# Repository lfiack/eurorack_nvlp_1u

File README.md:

# Eurorack NVLP 1U
Single Attack/Release envelope generator based on an STM32

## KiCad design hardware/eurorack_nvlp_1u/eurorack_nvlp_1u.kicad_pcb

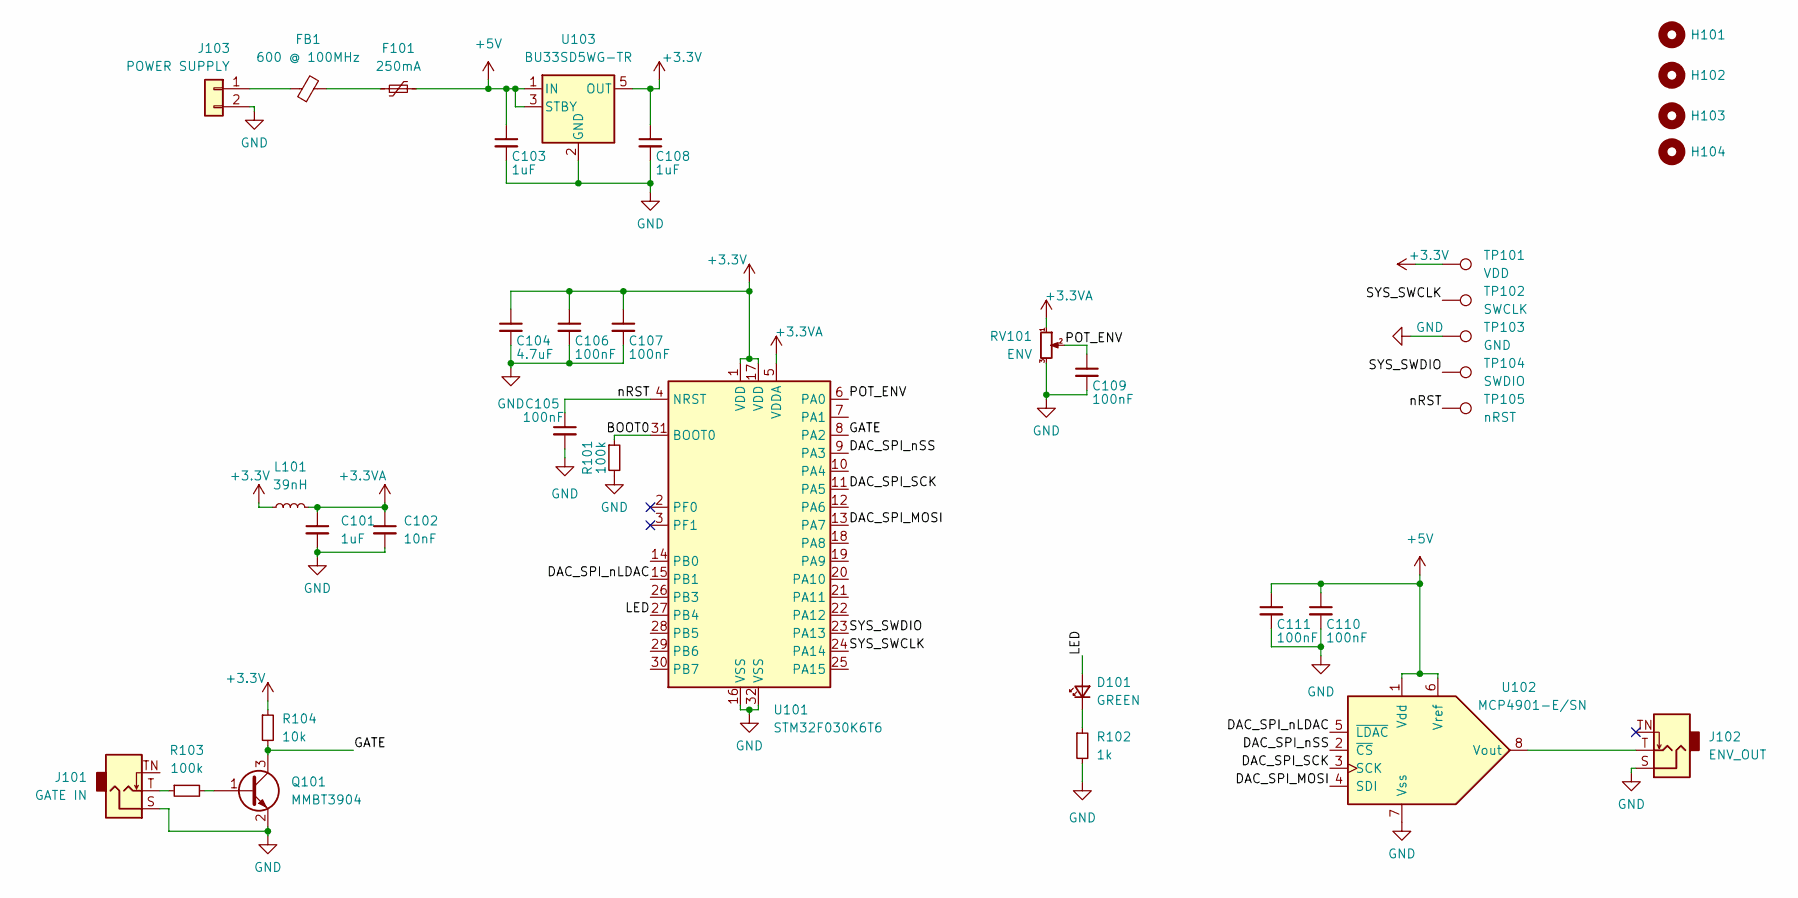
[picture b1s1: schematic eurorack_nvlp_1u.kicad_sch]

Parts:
C101, C103, C108: 1uF; C_0603_1608Metric
C102: 10nF; C_0603_1608Metric
C104: 4.7uF; C_0603_1608Metric
C105, C106, C107, C109, C110, C111: 100nF; C_0603_1608Metric
D101: GREEN; LED_0603_1608Metric
F101: 250mA; Fuse_1206_3216Metric; Farnell 2834880
FB1: 600 @ 100MHz; L_0805_2012Metric_Pad1.15x1.40mm_HandSolder; Farnell 2292460
H101, H102, H103, H104: MountingHole; MountingHole_3.2mm_M3
J101: GATE IN; Jack_3.5mm_QingPu_WQP-PJ398SM_Vertical_CircularHoles
J102: ENV_OUT; Jack_3.5mm_QingPu_WQP-PJ398SM_Vertical_CircularHoles
J103: POWER SUPPLY; JST_XH_B2B-XH-A_1x02_P2.50mm_Vertical
L101: 39nH; L_0603_1608Metric
Q101: MMBT3904; SOT-23
R101, R103: 100k; R_0603_1608Metric
R102: 1k; R_0603_1608Metric
R104: 10k; R_0603_1608Metric
RV101: ENV; Potentiometer_Alpha_RD901F-40-00D_Single_Vertical
TP101: VDD; TestPoint_Pad_D1.5mm
TP102: SWCLK; TestPoint_Pad_D1.5mm
TP103: GND; TestPoint_Pad_D1.5mm
TP104: SWDIO; TestPoint_Pad_D1.5mm
TP105: nRST; TestPoint_Pad_D1.5mm
U101: STM32F030K6T6; LQFP-32_7x7mm_P0.8mm
U102: MCP4901-E/SN; SOIC-8_3.9x4.9mm_P1.27mm
U103: BU33SD5WG-TR; SOT-23-5

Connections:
+3.3V: C104.1, C106.1, C107.1, C108.1, L101.1, R104.1, TP101.1, U101.1 (VDD), U101.17 (VDD), U103.5 (OUT)
+3.3VA: C101.1, C102.1, L101.2, RV101.1, U101.5 (VDDA)
+5V: C103.1, C110.1, C111.1, F101.2, U102.1 (Vdd), U102.6 (Vref), U103.1 (IN), U103.3 (STBY)
/BOOT0: R101.1, U101.31 (BOOT0)
/DAC_SPI_MOSI: U101.13 (PA7), U102.4 (SDI)
/DAC_SPI_SCK: U101.11 (PA5), U102.3 (SCK)
/DAC_SPI_nLDAC: U101.15 (PB1), U102.5 (~LDAC)
/DAC_SPI_nSS: U101.9 (PA3), U102.2 (~CS)
/GATE: Q101.3 (C), R104.2, U101.8 (PA2)
/LED: D101.2 (A), U101.27 (PB4)
/POT_ENV: C109.1, RV101.2, U101.6 (PA0)
/SYS_SWCLK: TP102.1, U101.24 (PA14)
/SYS_SWDIO: TP104.1, U101.23 (PA13)
/nRST: C105.1, TP105.1, U101.4 (NRST)
GND: C101.2, C102.2, C103.2, C104.2, C105.2, C106.2, C107.2, C108.2, C109.2, C110.2, C111.2, J101.S, J102.S, J103.2, Q101.2 (E), R101.2, R102.2, RV101.3, TP103.1, U101.16 (VSS), U101.32 (VSS), U102.7 (Vss), U103.2 (GND)
unnamed: D101.1 (K), R102.1
unnamed: F101.1, FB1.2
unnamed: J101.T, R103.1
unnamed: J102.T, U102.8 (Vout)
unnamed: FB1.1, J103.1
unnamed: Q101.1 (B), R103.2

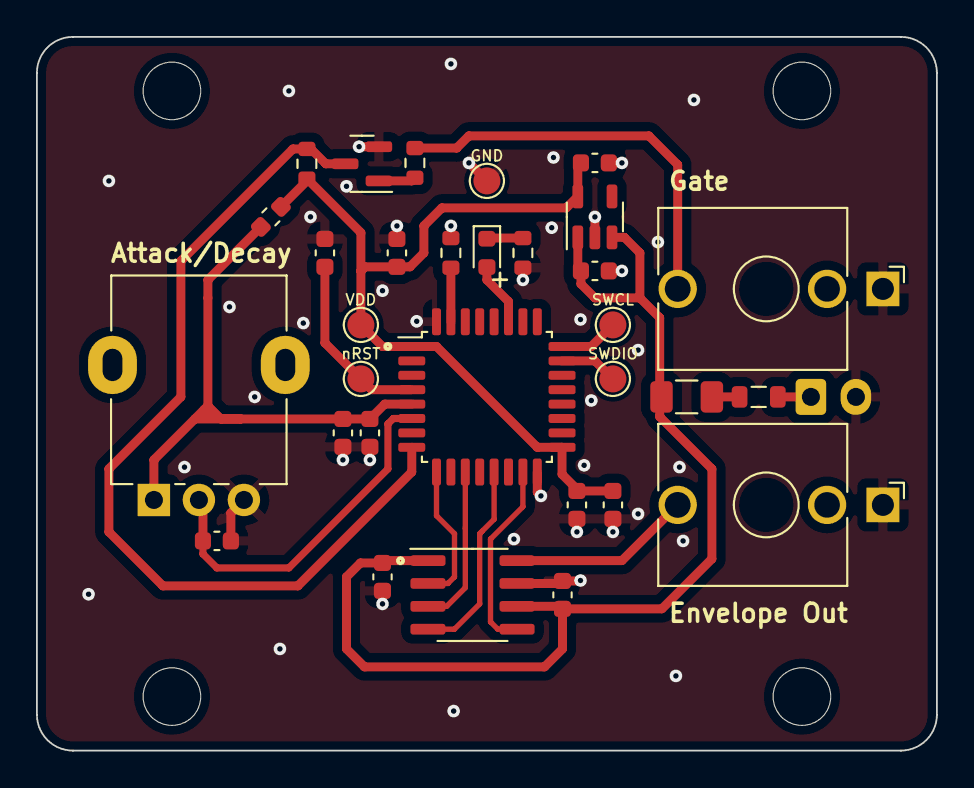
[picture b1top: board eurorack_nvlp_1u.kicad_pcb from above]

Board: 2 copper layers, 50.0 x 39.6 mm, 36 parts (1 on the bottom side), 21 nets.

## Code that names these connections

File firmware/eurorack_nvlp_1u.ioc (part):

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Mcu.Name=STM32F030K6Tx
Mcu.Package=LQFP32
Mcu.UserName=STM32F030K6Tx
PA0.GPIOParameters=GPIO_Label
PA0.GPIO_Label=POT_ENV
PA0.Mode=IN0
PA0.Signal=ADC_IN0
PA13.Mode=Serial_Wire
PA13.Signal=SYS_SWDIO
PA14.Mode=Serial_Wire
PA14.Signal=SYS_SWCLK
PA2.GPIOParameters=GPIO_Label
PA2.GPIO_Label=GATE
PA2.Signal=GPXTI2
PA3.GPIOParameters=PinState,GPIO_Label
PA3.GPIO_Label=DAC_SPI_nSS
PA3.PinState=GPIO_PIN_SET
PA3.Signal=GPIO_Output
PA5.GPIOParameters=GPIO_Label
PA5.GPIO_Label=DAC_SPI_SCK
PA5.Mode=TX_Only_Simplex_Unidirect_Master
PA5.Signal=SPI1_SCK
PA7.GPIOParameters=GPIO_Label
PA7.GPIO_Label=DAC_SPI_MOSI
PA7.Mode=TX_Only_Simplex_Unidirect_Master
PA7.Signal=SPI1_MOSI
PB1.GPIOParameters=GPIO_Label
PB1.GPIO_Label=DAC_SPI_nLDAC
PB1.Signal=GPIO_Output
PB4.GPIOParameters=GPIO_Label
PB4.GPIO_Label=LED
PB4.Signal=S_TIM3_CH1
RCC.HSE_VALUE=16000000
RCC.SYSCLKFreq_VALUE=48000000
RCC.SYSCLKSource=RCC_SYSCLKSOURCE_PLLCLK
board=custom

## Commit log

2022-10-24 Schematics + PCB
2022-10-24 small upgrades on the PCB
2022-10-28 fichiers de fab
2022-11-17 started firmware with vscode
2022-11-21 potentiometer to A/D envelope
2022-11-22 nvlp code + tests
2022-11-23 fixed ADC configuration
2022-11-23 corrected SPI driver
2022-11-24 added an LFO mode
